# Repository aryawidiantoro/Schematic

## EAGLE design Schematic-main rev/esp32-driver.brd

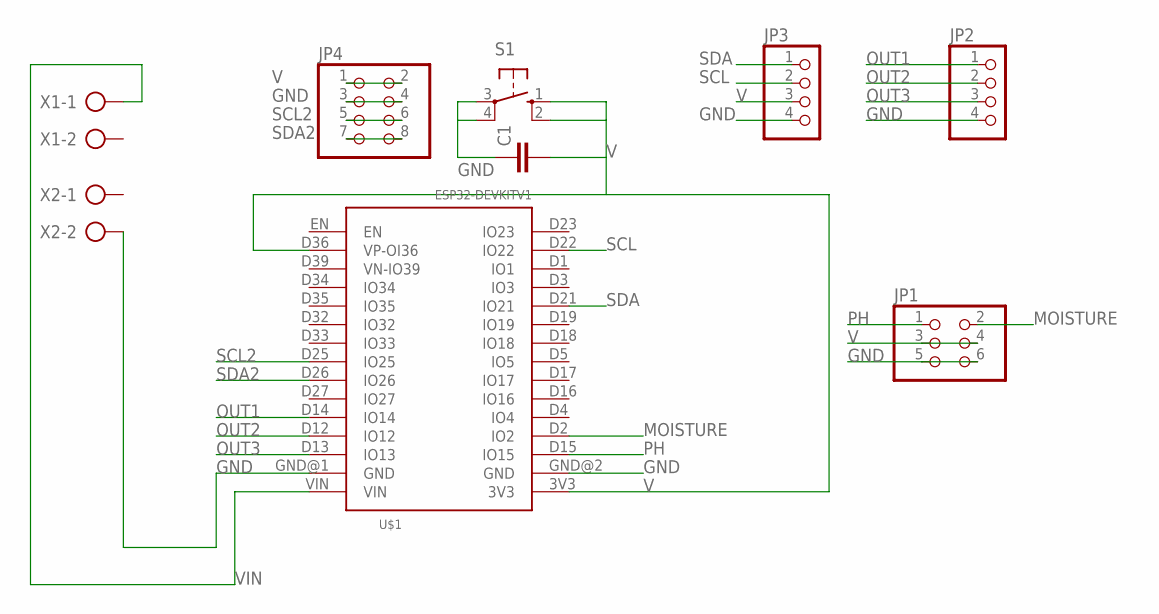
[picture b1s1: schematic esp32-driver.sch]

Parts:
C1: C-EU050-030X075; C050-030X075
JP1: PINHD-2X3; 2X03
JP2, JP3: PINHD-1X4; 1X04
JP4: PINHD-2X4; 2X04
S1: 10-XX; B3F-10XX
U$1: ESP32DEVKITV1; ESP32-DEVKITV1
X1, X2: AK300/2

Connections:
GND: C1.1, JP1.5, JP1.6, JP2.4, JP3.4, JP4.3, JP4.4, S1.3, S1.4 (P1), U$1.GND@1 (GND), U$1.GND@2 (GND), X2.2
MOISTURE: JP1.2, U$1.D2 (IO2)
OUT1: JP2.1, U$1.D14 (IO14)
OUT2: JP2.2, U$1.D12 (IO12)
OUT3: JP2.3, U$1.D13 (IO13)
PH: JP1.1, U$1.D15 (IO15)
SCL: JP3.2, U$1.D22 (IO22)
SCL2: JP4.5, JP4.6, U$1.D25 (IO25)
SDA: JP3.1, U$1.D21 (IO21)
SDA2: JP4.7, JP4.8, U$1.D26 (IO26)
V: C1.2, JP1.3, JP1.4, JP3.3, JP4.1, JP4.2, S1.1 (S), S1.2 (S1), U$1.3V3, U$1.D36 (VP-OI36)
VIN: U$1.VIN, X1.1

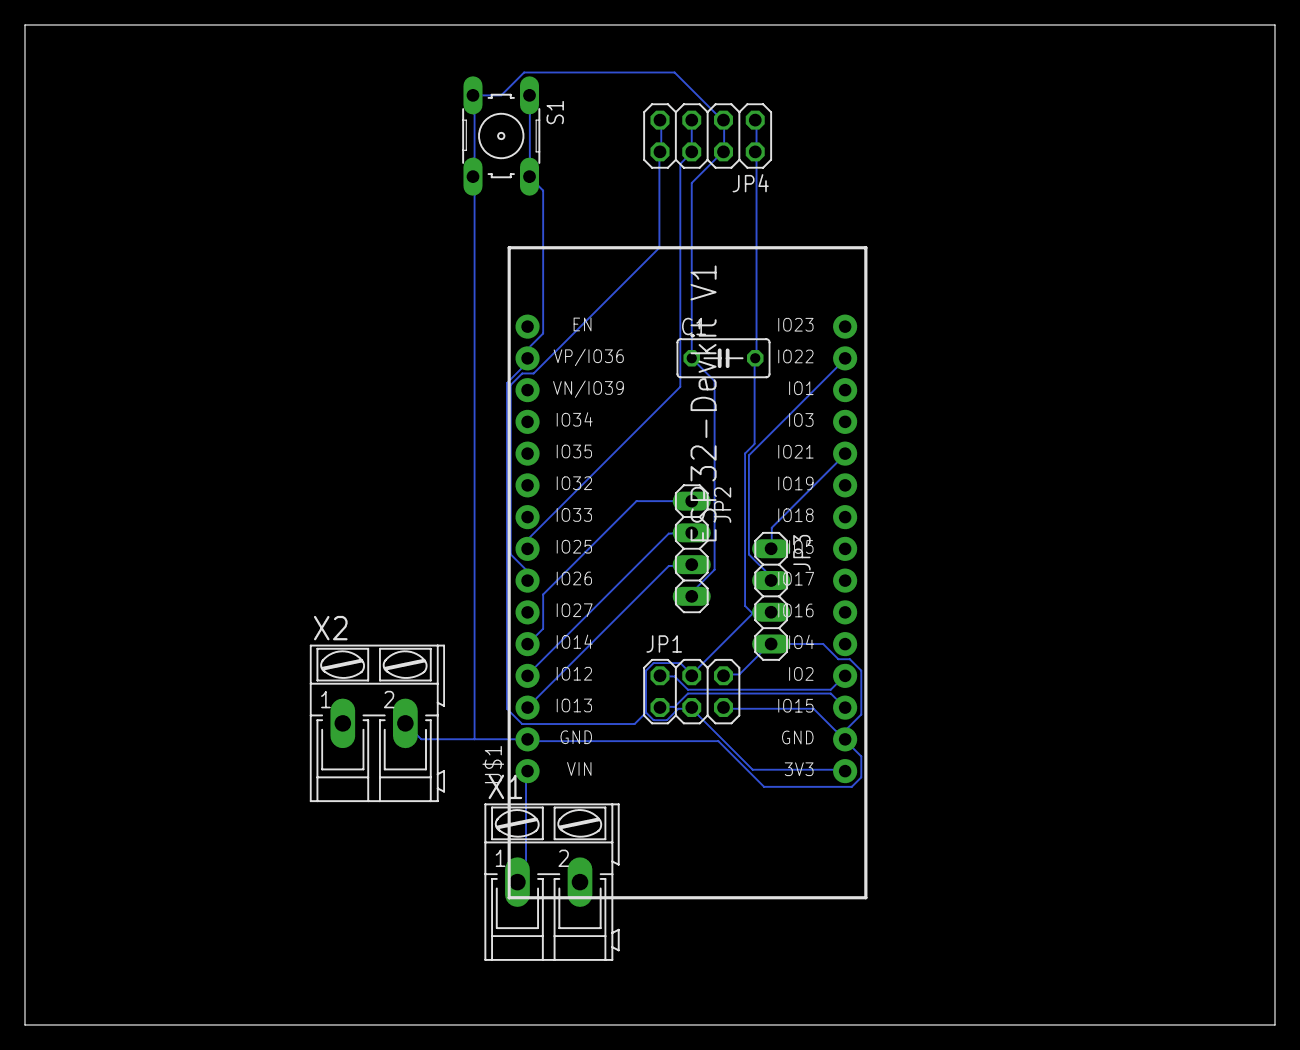
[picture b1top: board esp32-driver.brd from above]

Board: 2 copper layers, 100.0 x 80.0 mm, 9 parts (0 on the bottom side), 12 nets.

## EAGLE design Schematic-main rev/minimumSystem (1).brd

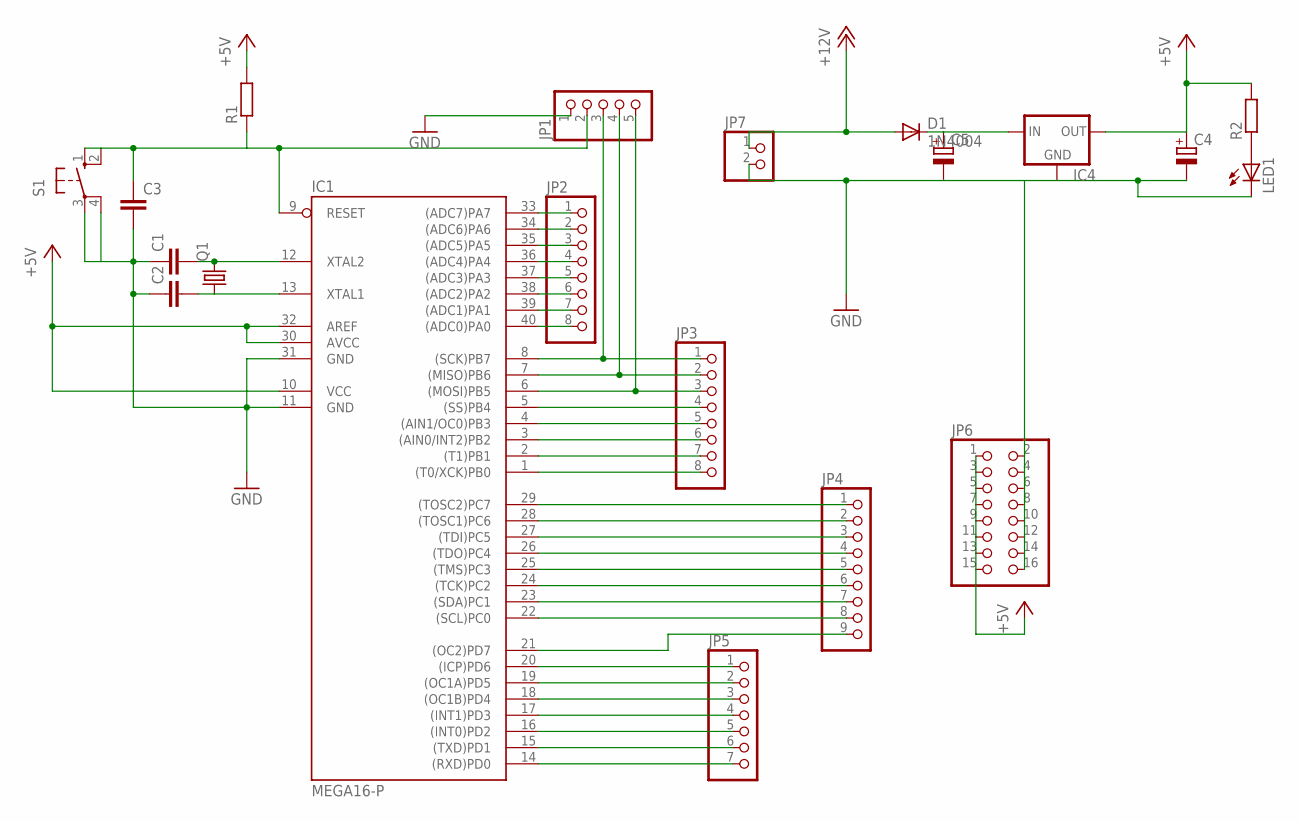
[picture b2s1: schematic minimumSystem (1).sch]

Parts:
C1, C2: C-EU025-024X044; C025-024X044
C3: C-EU050-025X075; C050-025X075
C4, C5: CPOL-EUE2.5-5; E2,5-5
D1: 1N4004; DO41-10
IC1: MEGA16-P; DIL40
IC4: 78XXS
JP1: PINHD-1X5; 1X05
JP2, JP3: PINHD-1X8; 1X08
JP4: PINHD-1X9; 1X09
JP5: PINHD-1X7; 1X07
JP6: PINHD-2X8; 2X08
JP7: PINHD-1X2; 1X02
LED1: LED5MM
Q1: CRYSTALHC49U-V; HC49U-V
R1, R2: R-EU_0204/7; 0204/7
S1: 10-XX; B3F-10XX

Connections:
+5V: C4.+, IC1.10 (VCC), IC1.30 (AVCC), IC1.32 (AREF), IC4.OUT, JP6.1, JP6.3, JP6.5, JP6.7, JP6.9, JP6.11, JP6.13, JP6.15, R1.2, R2.2
+12V: D1.A, JP7.1
C0: IC1.22 ((SCL)PC0), JP4.8
C1: IC1.23 ((SDA)PC1), JP4.7
C2: IC1.24 ((TCK)PC2), JP4.6
C3: IC1.25 ((TMS)PC3), JP4.5
D7: IC1.14 ((RXD)PD0), JP5.7
GND: C1.1, C2.1, C3.2, C4.-, C5.-, IC1.11 (GND), IC1.31 (GND), IC4.GND, JP1.1, JP6.2, JP6.4, JP6.6, JP6.8, JP6.10, JP6.12, JP6.14, JP6.16, JP7.2, LED1.K (C), S1.3, S1.4 (P1)
unnamed: IC1.33 ((ADC7)PA7), JP2.1
unnamed: IC1.34 ((ADC6)PA6), JP2.2
unnamed: IC1.35 ((ADC5)PA5), JP2.3
unnamed: IC1.36 ((ADC4)PA4), JP2.4
unnamed: IC1.37 ((ADC3)PA3), JP2.5
unnamed: IC1.38 ((ADC2)PA2), JP2.6
unnamed: IC1.39 ((ADC1)PA1), JP2.7
unnamed: IC1.40 ((ADC0)PA0), JP2.8
unnamed: IC1.29 ((TOSC2)PC7), JP4.1
unnamed: IC1.28 ((TOSC1)PC6), JP4.2
unnamed: IC1.27 ((TDI)PC5), JP4.3
unnamed: IC1.5 ((SS)PB4), JP3.4
unnamed: IC1.20 ((ICP)PD6), JP5.1
unnamed: IC1.19 ((OC1A)PD5), JP5.2
unnamed: IC1.26 ((TDO)PC4), JP4.4
unnamed: IC1.6 ((MOSI)PB5), JP1.5, JP3.3
unnamed: IC1.4 ((AIN1/OC0)PB3), JP3.5
unnamed: IC1.3 ((AIN0/INT2)PB2), JP3.6
unnamed: IC1.2 ((T1)PB1), JP3.7
unnamed: IC1.1 ((T0/XCK)PB0), JP3.8
unnamed: C5.+, D1.C, IC4.IN
unnamed: IC1.15 ((TXD)PD1), JP5.6
unnamed: IC1.16 ((INT0)PD2), JP5.5
unnamed: IC1.17 ((INT1)PD3), JP5.4
unnamed: C3.1, IC1.9 (RESET), JP1.2, S1.1 (S), S1.2 (S1)
unnamed: IC1.18 ((OC1B)PD4), JP5.3
unnamed: C1.2, IC1.12 (XTAL2), Q1.2
unnamed: C2.2, IC1.13 (XTAL1), Q1.1
unnamed: LED1.A, R2.1
unnamed: IC1.8 ((SCK)PB7), JP1.3, JP3.1
unnamed: IC1.7 ((MISO)PB6), JP1.4, JP3.2
RS: IC1.21 ((OC2)PD7), JP4.9

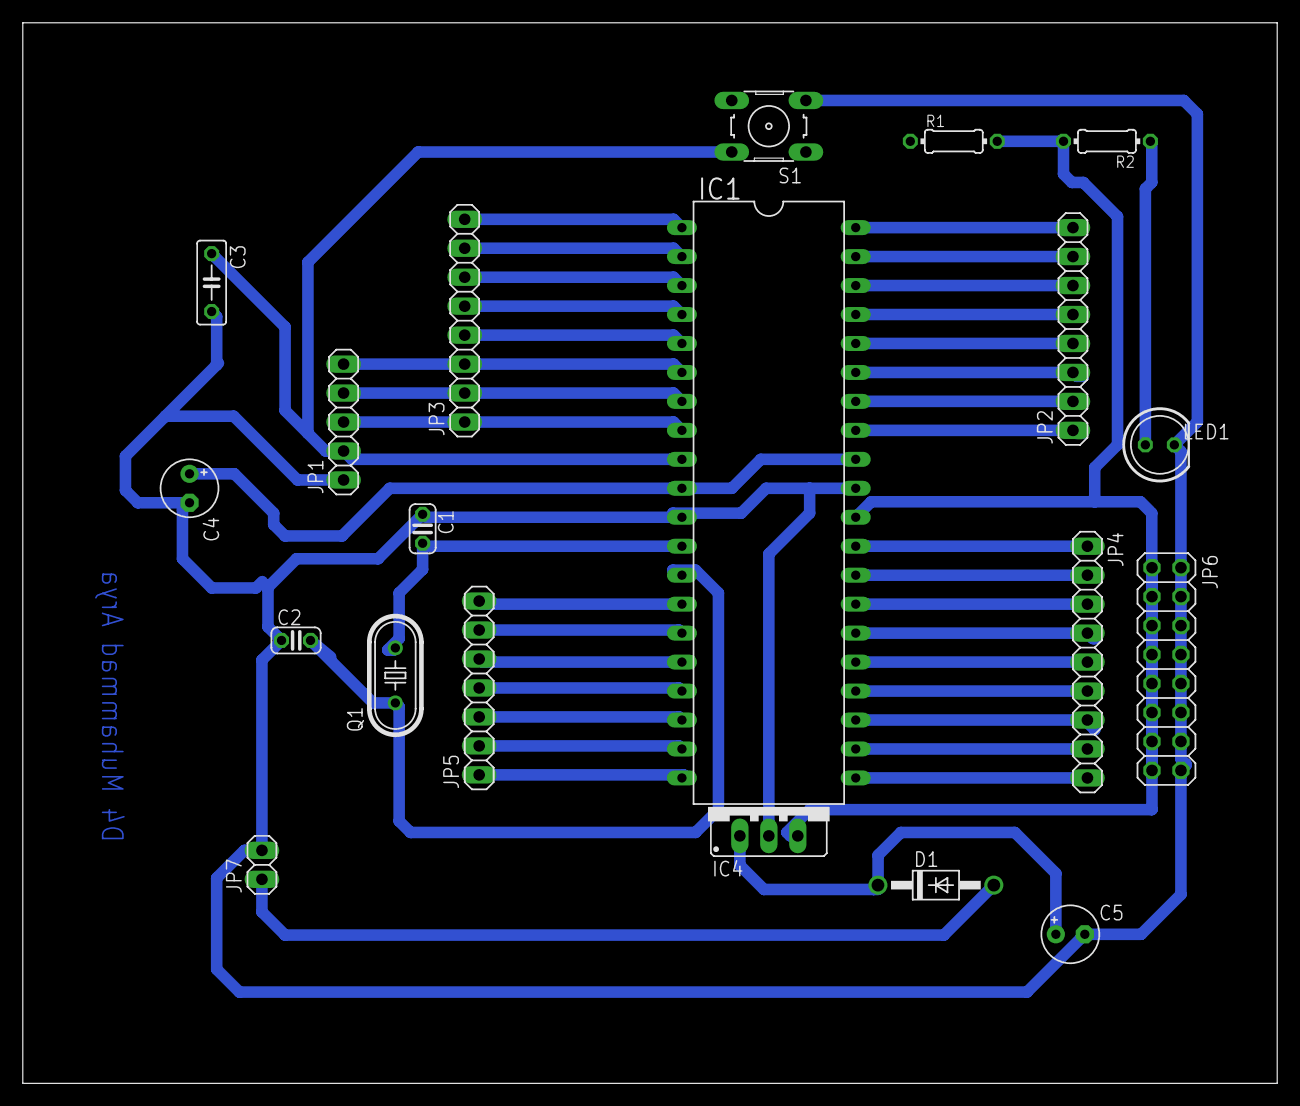
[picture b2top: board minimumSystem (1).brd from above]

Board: 2 copper layers, 110.0 x 93.0 mm, 20 parts (0 on the bottom side), 40 nets.

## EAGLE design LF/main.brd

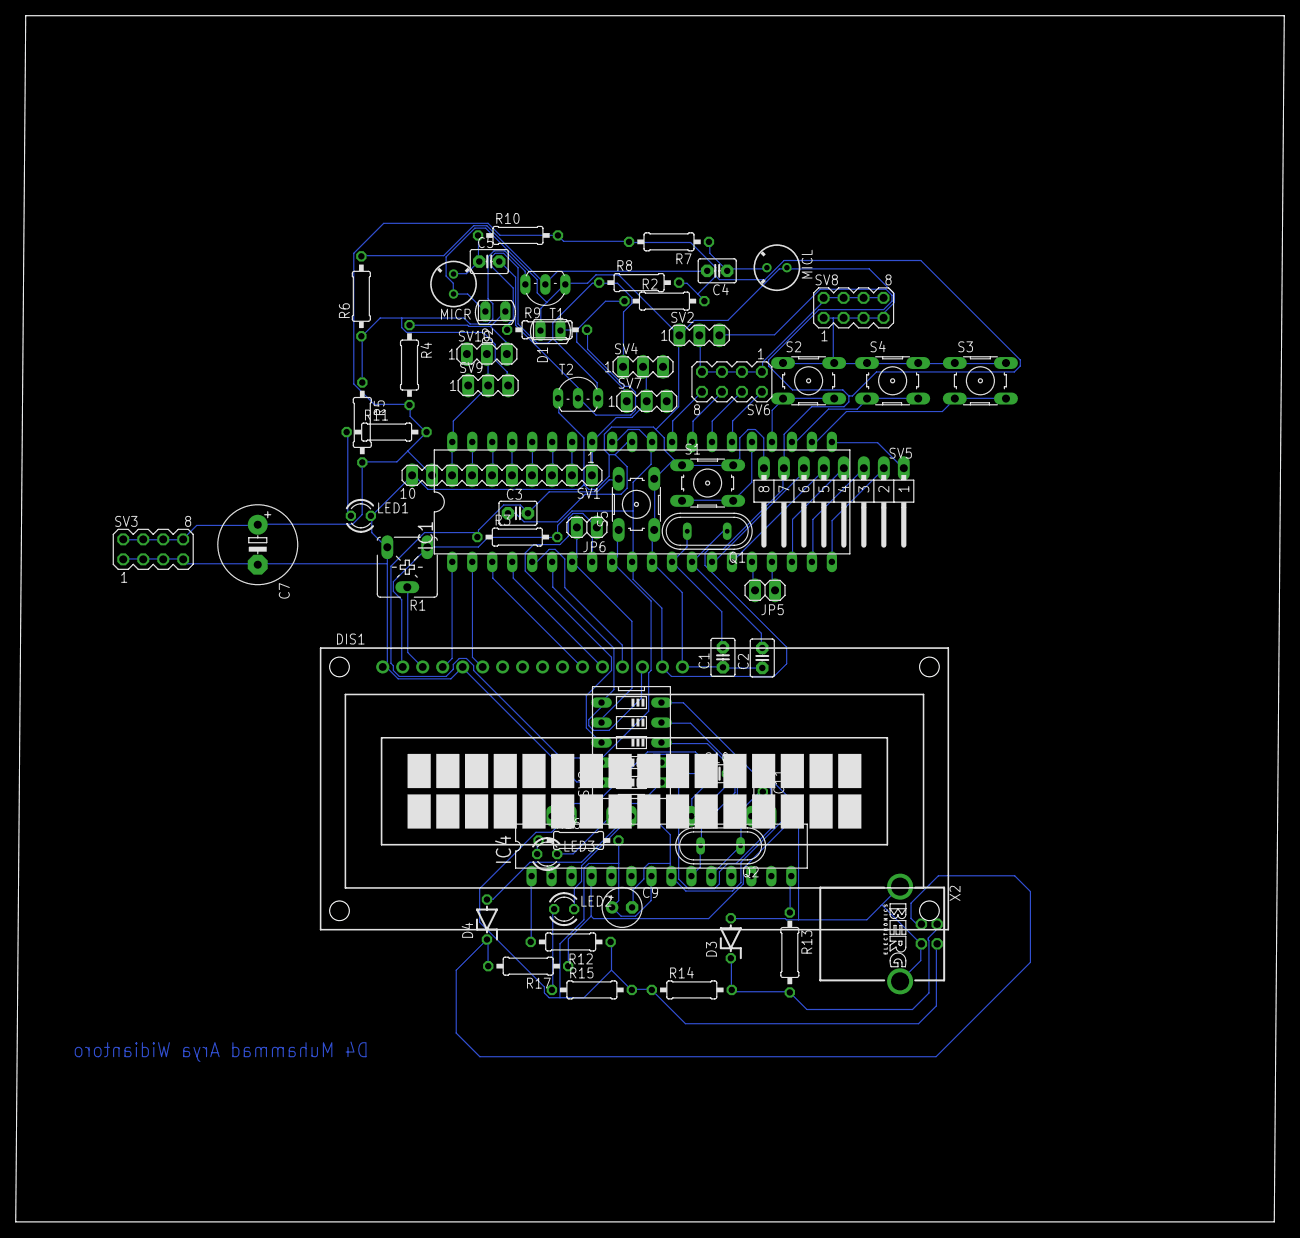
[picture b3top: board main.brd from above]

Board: 2 copper layers, 161.3 x 153.3 mm, 61 parts (0 on the bottom side), 65 nets.

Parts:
C1, C2: 22p; C2.5-3
C3: 10nF; C2.5-3
C4, C5: 100nF; C2.5-3
C7: 1000uF/16V; E5-10,5
C9: 10uF/16V; E2,5-5
C10, C11: 22pF; C025-024X044
D1, D2: SFH225
D3, D4: DZ3,6V; ZDIO-5
DIS1: TUXGR_16X2_R2
IC1: MEGA16-P; DIL40
IC4: MEGA8-P; DIL28-3
JP5, JP6: 1X02
LED1: merah; LED3MM
LED2: Merah; LED3MM
LED3: hijau; LED3MM
MICL: MC; F6050AP
MICR: MC; F6050AP
Q1: 8MHz; QS
Q2: 12MHz; QS
R1: 20K; CA6V
R2, R4: 56K; 0207/10
R3, R5, R7, R8, R10, R12: 10K; 0207/10
R6, R9: 100K; 0207/10
R11, R15, R16: 330; 0207/10
R13, R17: 68; 0207/10
R14: 2K2; 0207/10
S1, S2, S3, S4, S5: B3F-10XX
SV1: MA10-1
SV2, SV4, SV7, SV9, SV10: MA03-1
SV3, SV6, SV8: MA04-2
SV5: MA08-1W
SW2: EDG-05
T1, T2: TO92-EBC
X2: PN61729-S

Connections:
DGND: C9.-, C10.1, C11.1, D3.A, D4.A, IC4.8, IC4.22, SW2.1, X2.4, X2.S1, X2.S2
GND: C1.1, C2.1, C3.1, C7.-, D1.K, D2.K, DIS1.1, DIS1.5, DIS1.16, IC1.11, IC1.31, LED1.K, MICL.1, MICR.1, R1.E, S1.1, S1.2, S2.1, S2.2, S3.1, S3.2, S4.1, S4.2, S5.3, S5.4, SV1.10, SV2.1, SV3.1, SV3.3, SV3.5, SV3.7, SV5.8, SV8.1, SV8.3, SV8.5, SV8.7, SW2.10, T1.E, T2.E
MISO: IC1.7, JP6.2, SW2.7
MOSI: DIS1.14, IC1.6, SW2.6
unnamed: IC1.33, SV1.1, SV4.2, SV7.2
unnamed: IC1.34, SV1.2
unnamed: IC1.35, SV1.3
unnamed: IC1.36, SV1.4
unnamed: IC1.37, SV1.5
unnamed: IC1.38, SV1.6
unnamed: IC1.39, SV1.7
unnamed: D2.A, R4.1, SV10.3
unnamed: IC1.24, S2.3, S2.4
unnamed: DIS1.13, IC1.5
unnamed: DIS1.12, IC1.4
unnamed: DIS1.11, IC1.3
unnamed: DIS1.6, IC1.2
unnamed: R5.1, R6.1, SV9.3, T1.C
unnamed: DIS1.3, R1.S
unnamed: C1.2, IC1.12, Q1.2
unnamed: C2.2, IC1.13, Q1.1
unnamed: DIS1.4, IC1.1
unnamed: D1.A, R2.1, SV7.1
unnamed: IC1.23, S4.3, S4.4
unnamed: IC1.40, SV1.8, SV9.2, SV10.2
unnamed: C4.2, R6.2, T1.B
unnamed: C4.1, MICL.2, R7.1
unnamed: R8.1, R9.1, SV4.1, T2.C
unnamed: C5.2, R9.2, T2.B
unnamed: C5.1, MICR.2, R10.1
unnamed: IC1.22, S3.3, S3.4
unnamed: IC1.25, S1.3, S1.4
unnamed: IC1.21, SV5.1
unnamed: IC1.20, SV5.2
unnamed: IC1.19, SV5.3
unnamed: IC1.18, SV5.4
unnamed: IC1.15, SV5.5
unnamed: IC1.14, SV5.6
unnamed: IC1.16, JP5.2
unnamed: IC1.17, JP5.1
unnamed: LED1.A, R11.1
unnamed: IC4.1, R12.2
unnamed: IC1.26, SV6.2
unnamed: IC1.27, SV6.4
unnamed: IC1.28, SV6.6
unnamed: IC1.29, SV6.8
unnamed: C10.2, IC4.9, Q2.2
unnamed: C11.2, IC4.10, Q2.1
unnamed: IC4.14, R13.1
unnamed: LED2.A, R15.1
unnamed: LED3.A, R16.1
unnamed: IC4.23, LED2.K
unnamed: IC4.24, LED3.K
unnamed: D4.C, R17.2, X2.3
unnamed: IC4.4, IC4.15, R17.1
unnamed: D3.C, R13.2, R14.2, X2.2
unnamed: IC4.17, SW2.5
unnamed: IC4.18, SW2.4
unnamed: IC4.19, SW2.3
unnamed: IC4.16, SW2.2
RESET: C3.2, IC1.9, R3.1, S5.1, S5.2, SW2.9
SCK: IC1.8, JP6.1, SW2.8
VCC: C7.+, DIS1.2, DIS1.15, IC1.10, IC1.30, IC1.32, R1.A, R2.2, R3.2, R4.2, R5.2, R7.2, R8.2, R10.2, R11.2, SV1.9, SV2.3, SV3.2, SV3.4, SV3.6, SV3.8, SV5.7
VDD: SV2.2, SV6.1, SV6.3, SV6.5, SV6.7, SV8.2, SV8.4, SV8.6, SV8.8
VPP: C9.+, IC4.7, IC4.20, R12.1, R14.1, R15.2, R16.2, X2.1

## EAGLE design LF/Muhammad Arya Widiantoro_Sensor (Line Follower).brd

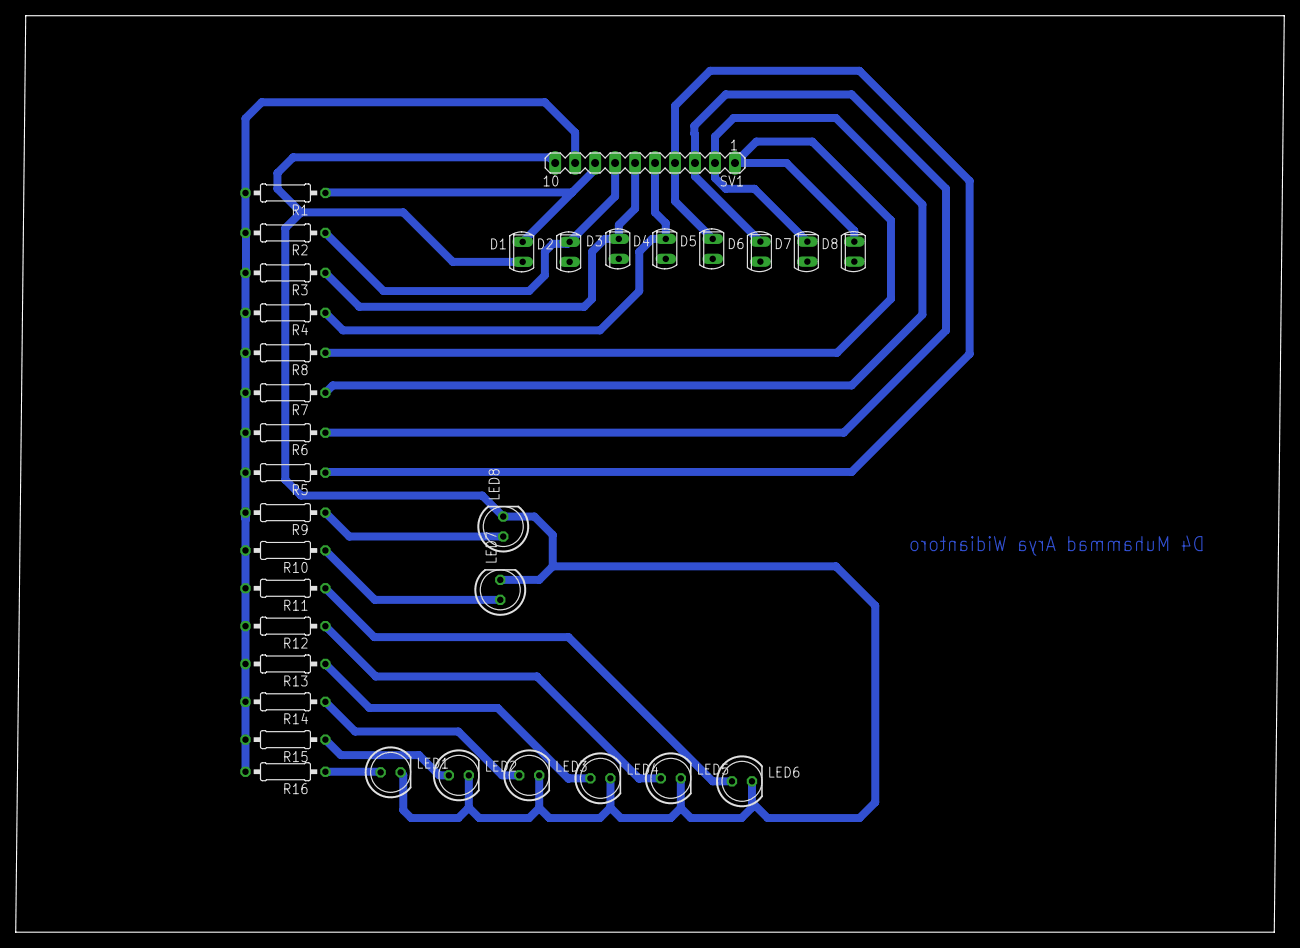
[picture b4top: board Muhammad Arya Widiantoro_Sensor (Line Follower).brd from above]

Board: 2 copper layers, 161.3 x 116.5 mm, 33 parts (0 on the bottom side), 18 nets.

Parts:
D1, D2, D3, D4, D5, D6, D7, D8: PhotoDioda; SFH225
LED1, LED2, LED3, LED4, LED5, LED6, LED7, LED8: LED putih SB; LED5MM
R1, R2, R3, R4, R5, R6, R7, R8: 0207/10
R9, R10, R11, R12, R13, R14, R15, R16: 330; 0207/10
SV1: MA10-1

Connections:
GND: D1.A, D2.A, D3.A, D4.A, D5.A, D6.A, D7.A, D8.A, LED1.K, LED2.K, LED3.K, LED4.K, LED5.K, LED6.K, LED7.K, LED8.K, SV1.10
unnamed: LED7.A, R10.1
unnamed: D7.K, R7.1, SV1.2
unnamed: D8.K, R8.1, SV1.1
unnamed: D1.K, R1.1, SV1.8
unnamed: D2.K, R2.1, SV1.7
unnamed: D3.K, R3.1, SV1.6
unnamed: D5.K, R5.1, SV1.4
unnamed: D4.K, R4.1, SV1.5
unnamed: D6.K, R6.1, SV1.3
unnamed: LED6.A, R11.1
unnamed: LED5.A, R12.1
unnamed: LED4.A, R13.1
unnamed: LED3.A, R14.1
unnamed: LED2.A, R15.1
unnamed: LED1.A, R16.1
unnamed: LED8.A, R9.1
VCC: R1.2, R2.2, R3.2, R4.2, R5.2, R6.2, R7.2, R8.2, R9.2, R10.2, R11.2, R12.2, R13.2, R14.2, R15.2, R16.2, SV1.9

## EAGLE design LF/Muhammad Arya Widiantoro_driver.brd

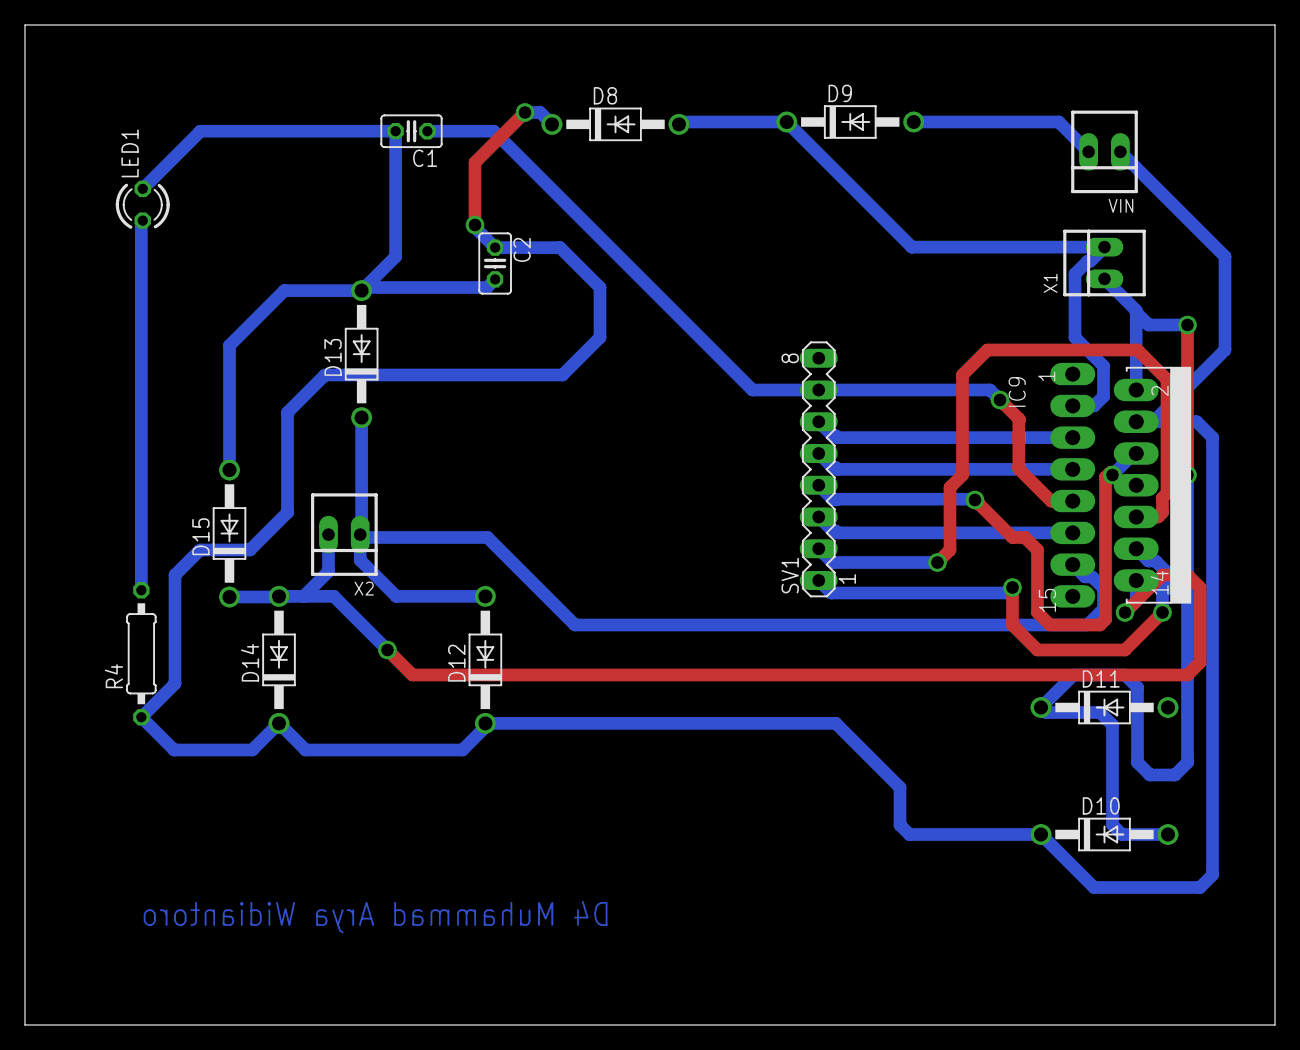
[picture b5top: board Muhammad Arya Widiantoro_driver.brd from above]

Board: 2 copper layers, 100.0 x 80.0 mm, 17 parts (0 on the bottom side), 14 nets.

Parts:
C1, C2: 100nF; C025-025X050
D8, D9, D10, D11, D12, D13, D14, D15: 1N4004; DO41-10
IC9: L298; MULTIWATT-15
LED1: LED3MM
R4: 330; 0207/10
SV1: MA08-1
VIN: 22-23-2021
X1, X2: 22-23-2021

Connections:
GND: C1.2, C2.2, D9.A, D11.A, D13.A, D15.A, IC9.1, IC9.8, IC9.15, LED1.K, SV1.8, VIN.2
unnamed: IC9.5, SV1.6
unnamed: IC9.7, SV1.5
unnamed: IC9.12, SV1.1
unnamed: IC9.10, SV1.2
unnamed: IC9.6, SV1.4
unnamed: IC9.11, SV1.3
unnamed: LED1.A, R4.2
unnamed: D8.A, D9.C, IC9.3, X1.2
unnamed: D10.A, D11.C, IC9.2, X1.1
unnamed: D12.A, D13.C, IC9.13, X2.1
unnamed: D14.A, D15.C, IC9.14, X2.2
VCC: C1.1, IC9.9, SV1.7
VDD: C2.1, D8.C, D10.C, D12.C, D14.C, IC9.4, R4.1, VIN.1

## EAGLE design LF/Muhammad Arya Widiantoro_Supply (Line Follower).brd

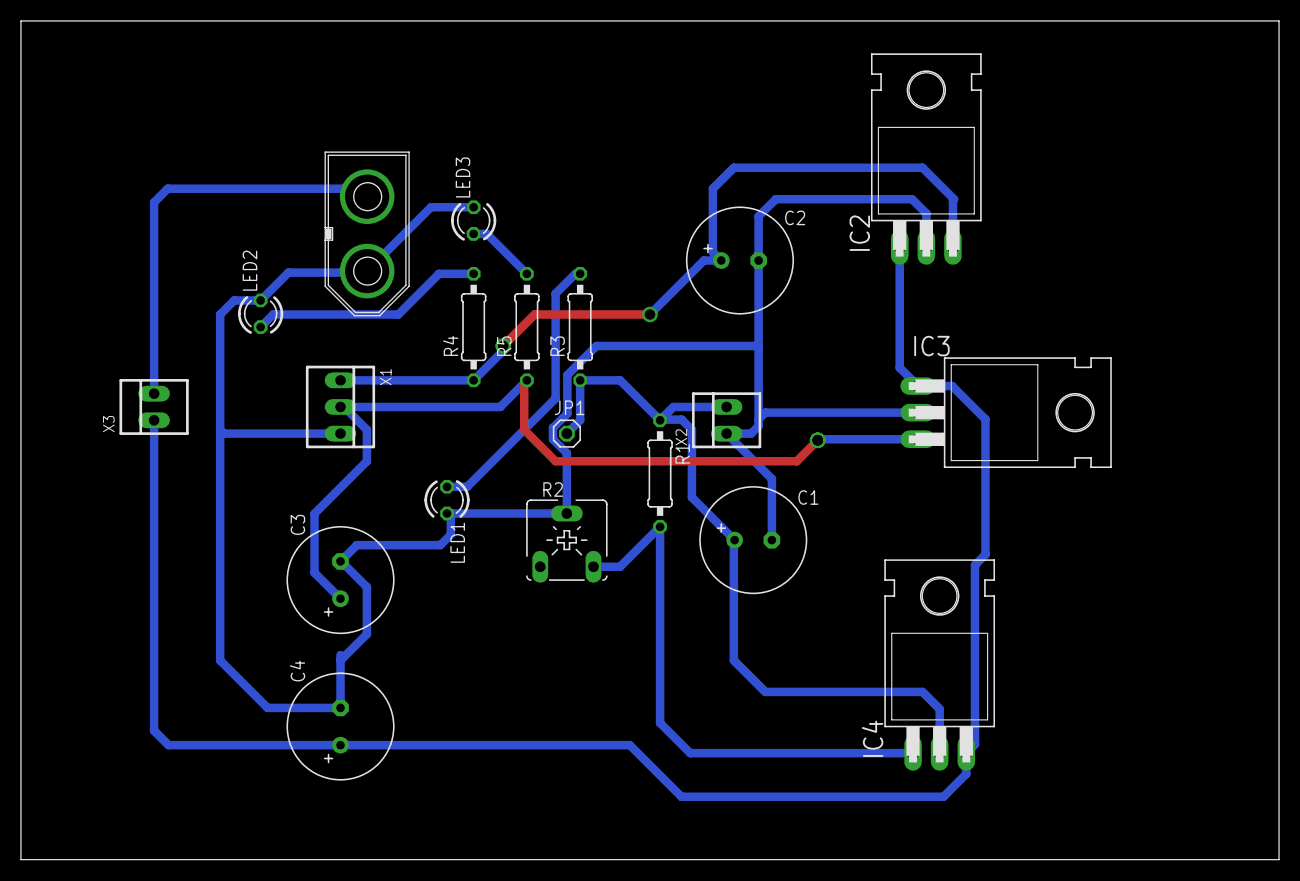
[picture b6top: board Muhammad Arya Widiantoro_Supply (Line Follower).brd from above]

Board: 2 copper layers, 120.0 x 80.0 mm, 20 parts (0 on the bottom side), 10 nets.

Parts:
C1, C2, C3, C4: 1000uF/16V; E3,5-10
IC2, IC3: 7805T; TO220H
IC4: 317T; TO220H
JP1: 1X01
LED1, LED2, LED3: LED3MM
R1: 1K2; 0207/10
R2: 20K; CA6V
R3, R4, R5: 1K; 0207/10
VIN: CON-XT60M
X1: VSYS; 22-23-2031
X2: VMOT; 22-23-2021
X3: switch; 22-23-2021

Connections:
+12V: C3.+, IC3.3, R5.1, X1.2
GND: C1.-, C2.-, C3.-, C4.-, IC2.2, IC3.2, LED1.K, LED2.K, LED3.K, R2.S, VIN.V-, X1.3, X2.1
unnamed: IC4.1, R1.2, R2.E
unnamed: LED1.A, R3.2
unnamed: LED3.A, R5.2
unnamed: VIN.V+, X3.2
unnamed: LED2.A, R4.2
VCC: C2.+, IC2.3, R4.1, X1.1
VDD: C1.+, IC4.2, JP1.1, R1.1, R3.1, X2.2
VPP: C4.+, IC2.1, IC3.1, IC4.3, X3.1

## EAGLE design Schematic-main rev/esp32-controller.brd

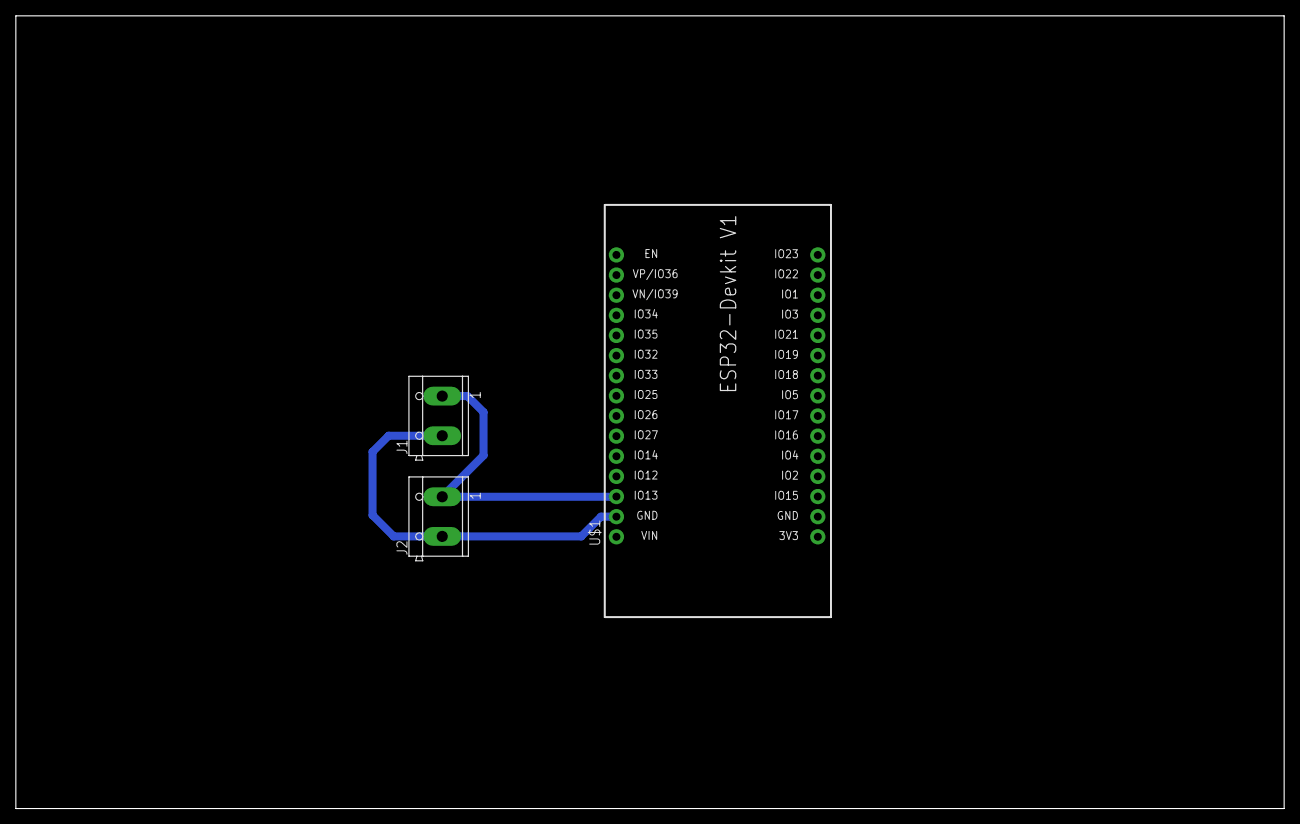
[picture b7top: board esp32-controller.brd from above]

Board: 2 copper layers, 160.0 x 100.0 mm, 3 parts (0 on the bottom side), 2 nets.

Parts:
J1, J2: CON_TERMINAL_BLOCK_02-5MM; TERMINAL_BLOCK_2P_5
U$1: ESP32DEVKITV1; ESP32-DEVKITV1

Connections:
GND: J1.1, J2.1, U$1.D13
HV: J1.2, J2.2, U$1.GND@1

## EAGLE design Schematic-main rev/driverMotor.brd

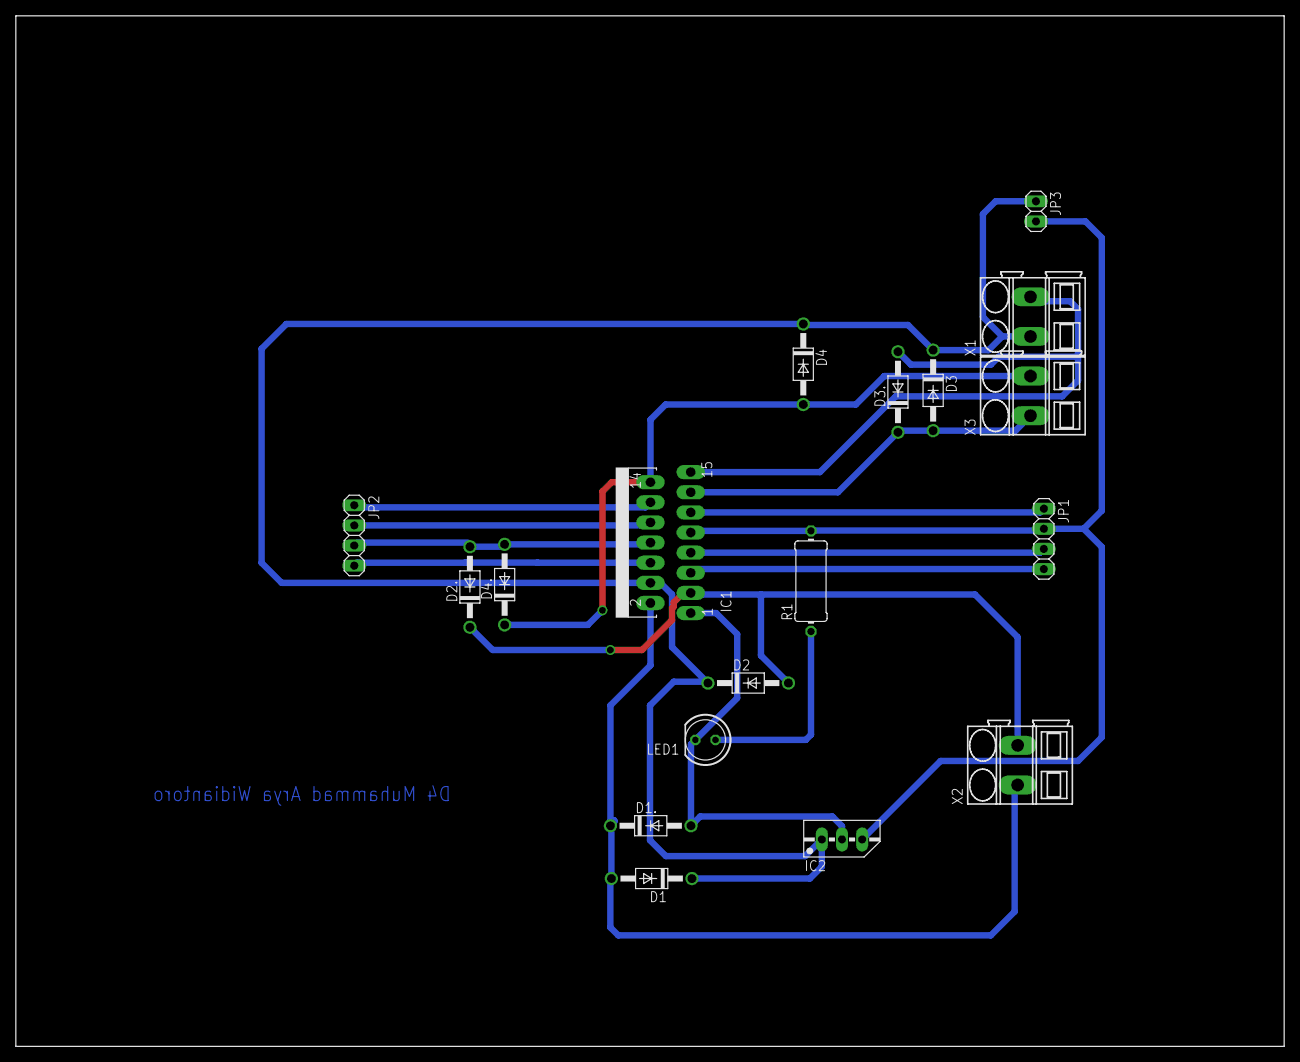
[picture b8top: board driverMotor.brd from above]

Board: 2 copper layers, 160.0 x 130.0 mm, 18 parts (0 on the bottom side), 14 nets.

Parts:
D1, D1., D2, D2., D3, D3., D4, D4.: 1N4004; DO41-10
IC1: L298; MULTIWATT-15
IC2: 78MXXS
JP1, JP2: 1X04
JP3: 1X02
LED1: LED5MM
R1: 0411/12
X1, X2, X3: SMKDSP_1,5/2

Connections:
+5V: IC1.9, IC2.OUT, JP1.2, JP3.2, R1.2
ENABLE_A: IC1.6, JP2.4
ENABLE_B: IC1.11, JP1.1
GND: D1..A, D2..A, D3..A, D4..A, IC1.1, IC1.8, IC1.15, IC2.GND, JP2.3, LED1.K, X1.2
INPUT1: IC1.5, JP1.4
INPUT2: IC1.7, JP1.3
INPUT3: IC1.10, JP2.2
INPUT4: IC1.12, JP2.1
LED: LED1.A, R1.1
MOTOR1_1: D1.A, D1..C, IC1.2, X2.1
MOTOR1_2: D2.A, D2..C, IC1.3, X2.2
MOTOR2_1: D3.A, D3..C, IC1.13, X3.1
MOTOR2_2: D4.A, D4..C, IC1.14, X3.2
VS: D1.C, D2.C, D3.C, D4.C, IC1.4, IC2.IN, JP3.1, X1.1

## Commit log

2021-12-04 Create Schematic-Main.
